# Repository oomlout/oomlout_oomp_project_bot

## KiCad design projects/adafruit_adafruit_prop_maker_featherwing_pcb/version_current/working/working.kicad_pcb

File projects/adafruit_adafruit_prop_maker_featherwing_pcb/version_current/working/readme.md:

# Adafruit-Prop-Maker-FeatherWing-PCB by adafruit  
This is a harvested standardized copy of a project from github.  
The original project can be found at:  
https://github.com/adafruit/Adafruit-Prop-Maker-FeatherWing-PCB  
Please consult that link for additional, details, files, and license information.  
Note: It was auto harvested and if the original repo had more than one board file or anything out of the ordinary the files here are likely not representative.

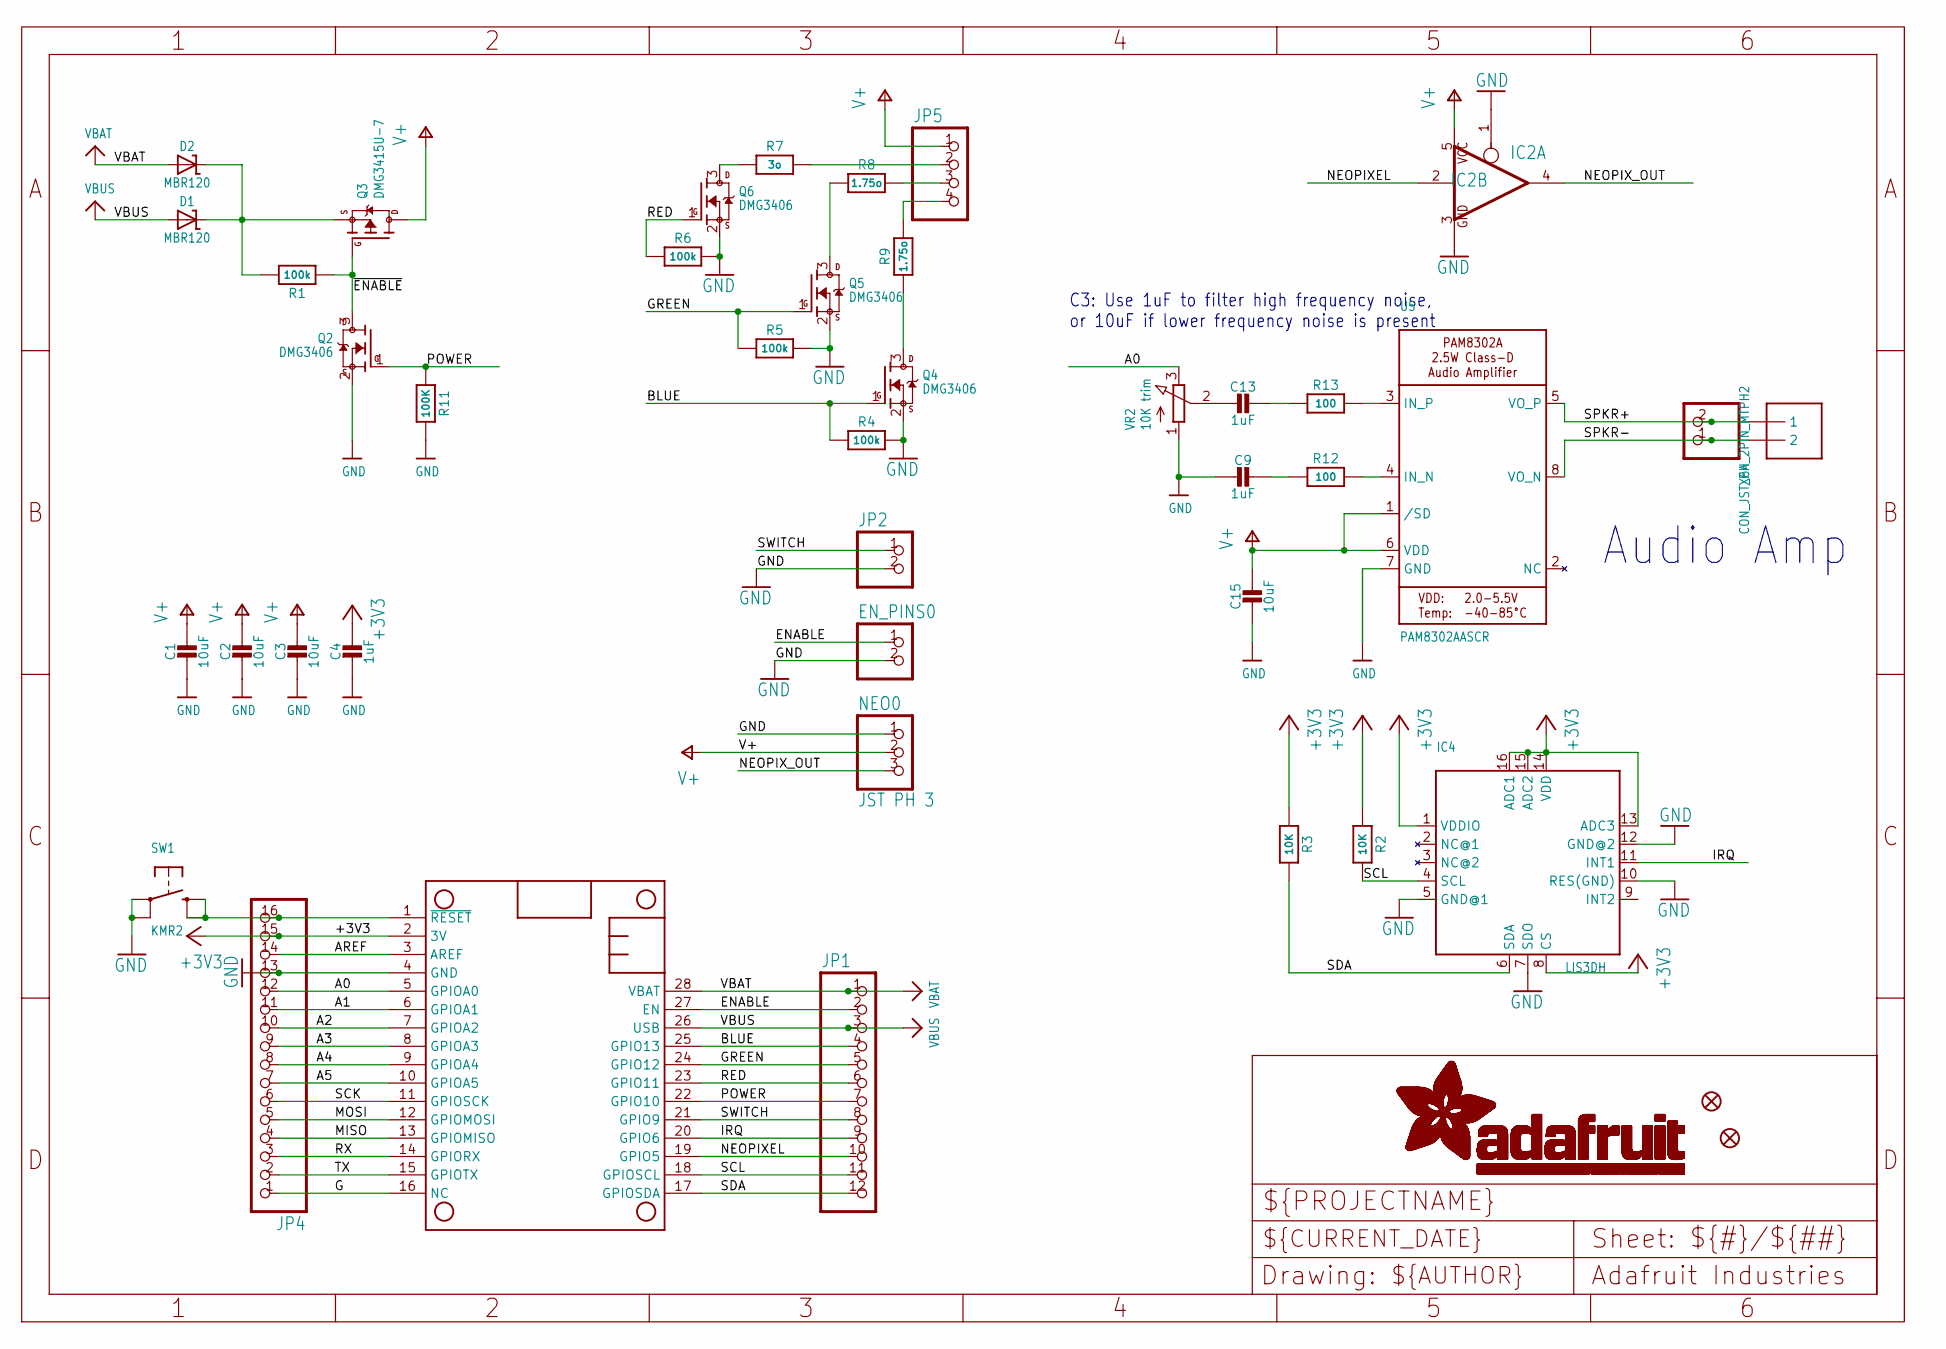
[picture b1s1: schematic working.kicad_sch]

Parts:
C1, C2, C3, C15: 10uF; 0805-NO
C4, C9, C13: 1uF; 0603-NO
D1, D2: MBR120; SOD-123
EN_PINS0: HEADER-1X2ROUND; 1X02_ROUND
FID1, FID3: FIDUCIAL_1MM
IC2: 741G125DBV; SOT23-5
IC4: LIS3DH; LGA16_3X3MM
JP1: HEADER-1X12; 1X12_ROUND
JP2: HEADER-1X2ROUND; 1X02_ROUND
JP4: HEADER-1X16ROUND; 1X16_ROUND
JP5: HEADER-1X4ROUND; 1X04_ROUND
MS1: FEATHERWING
NEO0: JST PH 3; JSTPH3
Q2, Q4, Q5, Q6: DMG3406; SOT23-WIDE
Q3: DMG3415U-7; SOT23-WIDE
R1, R4, R5, R6: 100k; 0603-NO
R2, R3: 10K; 0603-NO
R7: 3o; _1206
R8, R9: 1.75o; _1206
R11: 100K; 0603-NO
R12, R13: 100; 0603-NO
SW1: KMR2; BTN_KMR2_4.6X2.8
U5: PAM8302AASCR; MSOP8_0.65MM
U$1: CON_MOLEX_2P; 53398-0271
VR2: 10K trim; TRIMPOT_BOURNS_3303W
X6: CON_JST_PH_2PIN_MTPH2; JSTPH2

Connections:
+3V3: C4.1, IC4.1 (VDDIO), IC4.8 (CS), IC4.13 (ADC3), IC4.14 (VDD), IC4.15 (ADC2), IC4.16 (ADC1), JP4.15, MS1.2 (3V), R2.1, R3.1
A0: JP4.12, MS1.5 (GPIOA0), VR2.3 (E)
A1: JP4.11, MS1.6 (GPIOA1)
A2: JP4.10, MS1.7 (GPIOA2)
A3: JP4.9, MS1.8 (GPIOA3)
A4: JP4.8, MS1.9 (GPIOA4)
A5: JP4.7, MS1.10 (GPIOA5)
AREF: JP4.14, MS1.3 (AREF)
BLUE: JP1.4, MS1.25 (GPIO13), Q4.1 (G), R4.1
ENABLE: EN_PINS0.1, JP1.2, MS1.27 (EN)
G: JP4.1, MS1.16 (NC)
GND: C1.2, C2.2, C3.2, C4.2, C9.2, C15.2, EN_PINS0.2, IC2.1 (OE), IC2.3 (GND), IC4.5 (GND@1), IC4.7 (SDO), IC4.10 (RES(GND)), IC4.12 (GND@2), JP2.2, JP4.13, MS1.4 (GND), NEO0.1, Q2.2 (S), Q4.2 (S), Q5.2 (S), Q6.2 (S), R4.2, R5.2, R6.2, R11.2, SW1.A, SW1.A' (P1), U5.7 (GND), VR2.1 (A)
GREEN: JP1.5, MS1.24 (GPIO12), Q5.1 (G), R5.1
IRQ: IC4.11 (INT1), JP1.9, MS1.20 (GPIO6)
MISO: JP4.4, MS1.13 (GPIOMISO)
MOSI: JP4.5, MS1.12 (GPIOMOSI)
unnamed: Q6.3 (D), R7.1
unnamed: JP5.3, R8.2
unnamed: JP5.4, R9.2
unnamed: Q4.3 (D), R9.1
unnamed: Q5.3 (D), R8.1
unnamed: JP5.2, R7.2
unnamed: R12.2, U5.4 (IN_N)
unnamed: R13.2, U5.3 (IN_P)
unnamed: C9.1, R12.1
unnamed: C13.1, R13.1
unnamed: C13.2, VR2.2 (S)
unnamed: D1.C, D2.C, Q3.2 (S), R1.2
NEOPIXEL: IC2.2 (I), JP1.10, MS1.19 (GPIO5)
NEOPIX_OUT: IC2.4 (O), NEO0.3
POWER: JP1.7, MS1.22 (GPIO10), Q2.1 (G), R11.1
RED: JP1.6, MS1.23 (GPIO11), Q6.1 (G), R6.1
RESET: JP4.16, MS1.1 (~RESET), SW1.B (S), SW1.B' (S1)
RX: JP4.3, MS1.14 (GPIORX)
SCK: JP4.6, MS1.11 (GPIOSCK)
SCL: IC4.4 (SCL), JP1.11, MS1.18 (GPIOSCL), R2.2
SDA: IC4.6 (SDA), JP1.12, MS1.17 (GPIOSDA), R3.2
SPKR+: U5.5 (VO_P), U$1.1, X6.2
SPKR-: U5.8 (VO_N), U$1.2, X6.1
SWITCH: JP1.8, JP2.1, MS1.21 (GPIO9)
TX: JP4.2, MS1.15 (GPIOTX)
V+: C1.1, C2.1, C3.1, C15.1, IC2.5 (VCC), JP5.1, NEO0.2, Q3.3 (D), U5.1 (/SD), U5.6 (VDD)
VBAT: D2.A, JP1.1, MS1.28 (VBAT)
VBUS: D1.A, JP1.3, MS1.26 (USB)
~ENABLE: Q2.3 (D), Q3.1 (G), R1.1

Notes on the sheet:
Audio Amp
C3: Use 1uF to filter high frequency noise, or 10uF if lower frequency noise is present

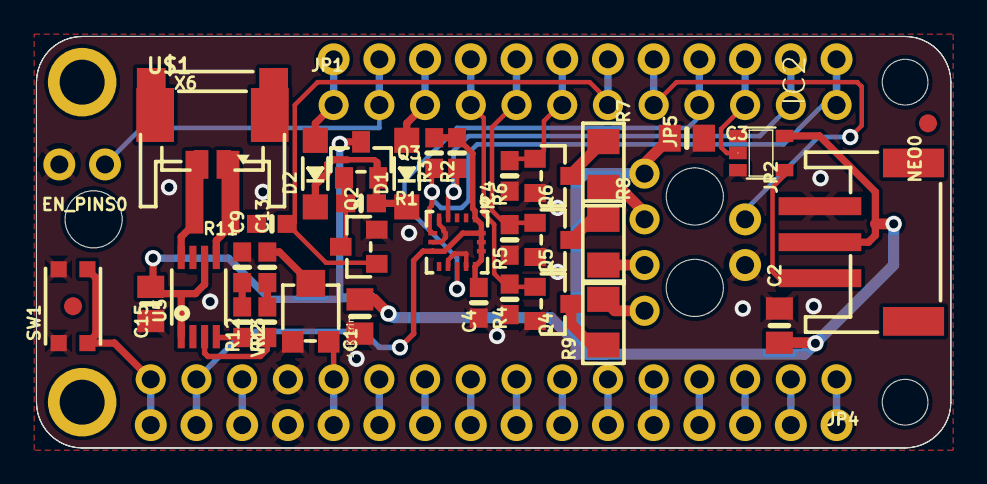
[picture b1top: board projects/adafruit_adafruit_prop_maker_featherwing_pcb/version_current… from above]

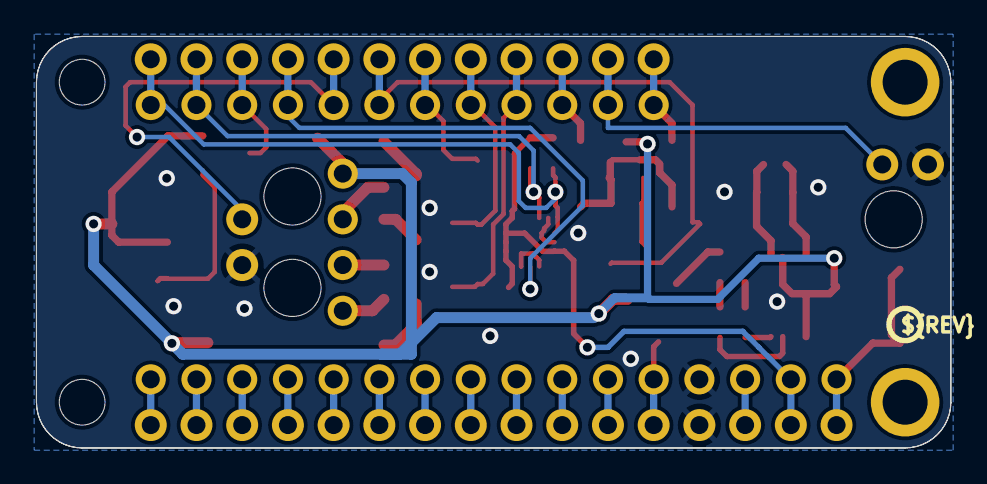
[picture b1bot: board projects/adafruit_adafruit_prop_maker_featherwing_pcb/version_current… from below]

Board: 2 copper layers, 50.8 x 22.9 mm, 48 parts (2 on the bottom side), 45 nets.

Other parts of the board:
@HOLE0, @HOLE1, @HOLE2: (no value)
U$6: PROPMAKER_BOT
U$14: PROPMAKER_TOP
U$15: PCBFEAT-REV-040

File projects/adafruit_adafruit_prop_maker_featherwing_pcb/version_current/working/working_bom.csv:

Row,Description,Part,References,Value,Footprint,Quantity Per PCB,Status,Datasheet
1,,CAP_CERAMIC0603_NO,C4 C9 C13,1uF,0603-NO,3, ,
2,,CAP_CERAMIC0805-NOOUTLINE,C1 C2 C3 C15,10uF,0805-NO,4, ,
3,,DIODE-SCHOTTKYSOD-123,D1 D2,MBR120,SOD-123,2, ,
4,,HEADER-1X2ROUND,EN_PINS0 JP2,HEADER-1X2ROUND,1X02_ROUND,2, ,
5,,741G125DBV,IC2,741G125DBV,SOT23-5,1, ,
6,,ACCEL_LIS3DHTR,IC4,LIS3DH,LGA16_3X3MM,1, ,
7,,HEADER-1X12,JP1,HEADER-1X12,1X12_ROUND,1, ,
8,,HEADER-1X16ROUND,JP4,HEADER-1X16ROUND,1X16_ROUND,1, ,
9,,HEADER-1X4ROUND,JP5,HEADER-1X4ROUND,1X04_ROUND,1, ,
10,,FEATHERWING,MS1,FEATHERWING,FEATHERWING,1, ,
11,,CON_JST_PH_3PIN,NEO0,JST PH 3,JSTPH3,1, ,
12,,MOSFET-NWIDE,Q2 Q4 Q5 Q6,DMG3406,SOT23-WIDE,4, ,
13,,MOSFET-PWIDE,Q3,DMG3415U-7,SOT23-WIDE,1, ,
14,,RESISTOR_1206,R8 R9,1.75o,_1206,2, ,
15,,RESISTOR_1206,R7,3o,_1206,1, ,
16,,RESISTOR_0603_NOOUT,R12 R13,100,0603-NO,2, ,
17,,RESISTOR_0603_NOOUT,R2 R3,10K,0603-NO,2, ,
18,,RESISTOR_0603_NOOUT,R1 R4 R5 R6 R11,100k,0603-NO,5, ,
19,,SWITCH_TACT_SMT4.6X2.8,SW1,KMR2,BTN_KMR2_4.6X2.8,1, ,
20,,AUDIOAMP_PAM8302A,U5,PAM8302AASCR,MSOP8_0.65MM,1, ,
21,,CON_MOLEX_2P,U$1,CON_MOLEX_2P,53398-0271,1, ,
22,,TRIMPOT3303W/X,VR2,10K trim,TRIMPOT_BOURNS_3303W,1, ,
23,,CON_JST_PH_2PIN_MTPH2,X6,CON_JST_PH_2PIN_MTPH2,JSTPH2,1, ,





Project info:
Schematic:,working
Variant:,default
Revision:,
Date:,2023-08-03_17-21-23
KiCad Version:,7.0.6-7.0.6~ubuntu22.04.1
Statistics:
Component Groups:,23
Component Count:,40 (0 SMD/ 0 THT)
Fitted Components:,40 (0 SMD/ 0 THT)
Number of PCBs:,1
Total Components:,40

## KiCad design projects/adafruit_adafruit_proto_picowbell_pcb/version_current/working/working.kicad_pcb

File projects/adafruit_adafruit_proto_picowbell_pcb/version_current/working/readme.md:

# Adafruit-Proto-PiCowbell-PCB by adafruit  
This is a harvested standardized copy of a project from github.  
The original project can be found at:  
https://github.com/adafruit/Adafruit-Proto-PiCowbell-PCB  
Please consult that link for additional, details, files, and license information.  
Note: It was auto harvested and if the original repo had more than one board file or anything out of the ordinary the files here are likely not representative.

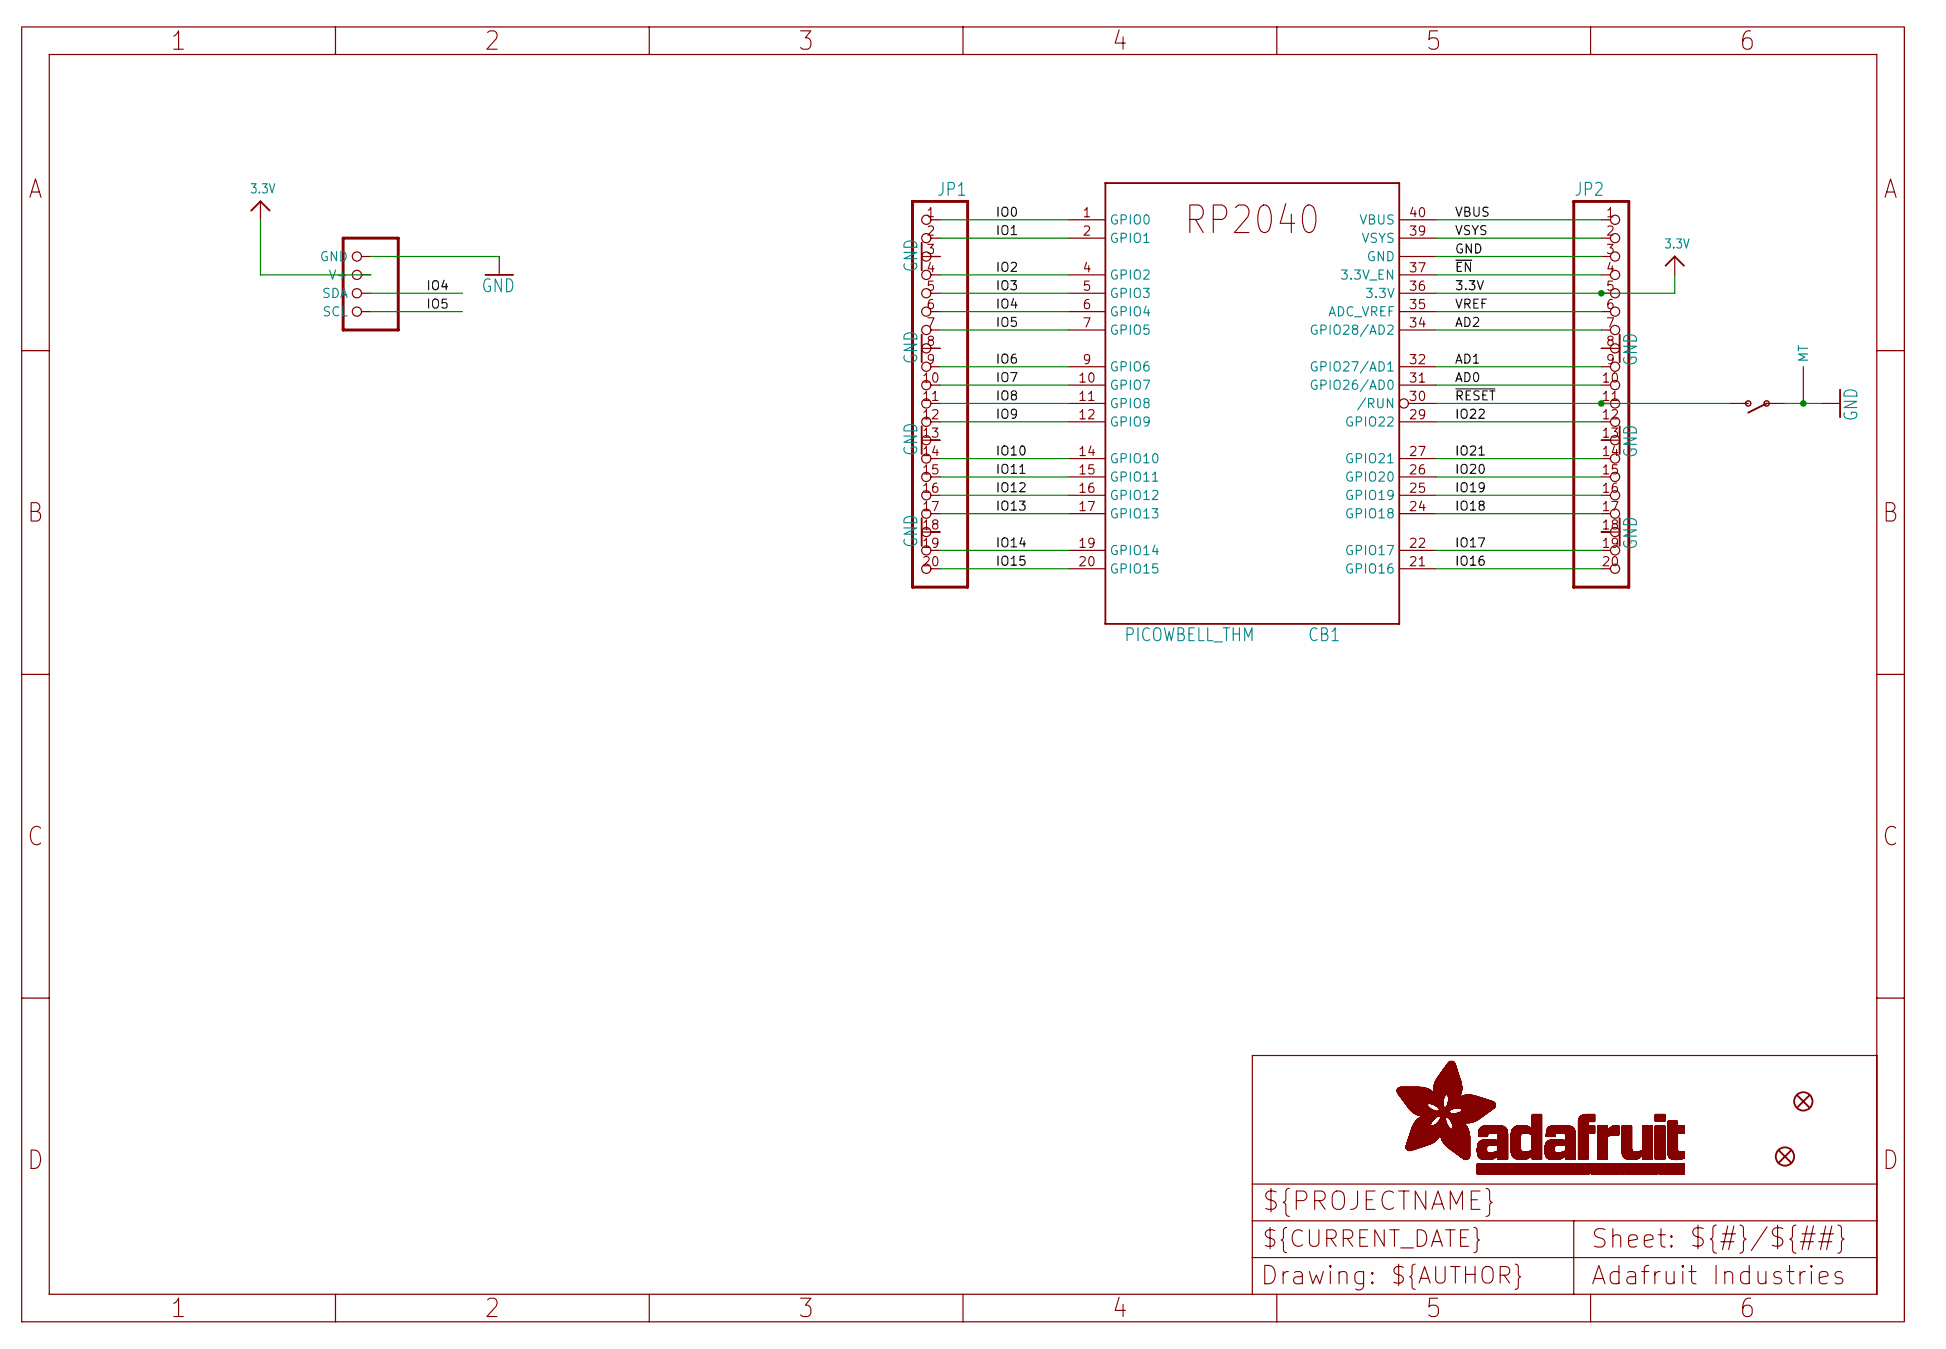
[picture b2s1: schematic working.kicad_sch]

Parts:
CB1: PICOWBELL_THM; PICOWBELL
CONN1: STEMMA_I2C_QT; JST_SH4
FID1, FID2: FIDUCIAL_1MM
JP1, JP2: HEADER-1X20_70MIL; 1X20_ROUND_70MIL
SW1: RA Tact; SPST_TACTILE_RA

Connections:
3.3V: CB1.36 (3.3V), CONN1.2 (V+), JP2.5
AD0: CB1.31 (GPIO26/AD0), JP2.10
AD1: CB1.32 (GPIO27/AD1), JP2.9
AD2: CB1.34 (GPIO28/AD2), JP2.7
GND: CB1.3 (GND), CB1.8 (GND), CB1.13 (GND), CB1.18 (GND), CB1.23 (GND), CB1.28 (GND), CB1.33 (GND), CB1.38 (GND), CONN1.1 (GND), JP1.3, JP1.8, JP1.13, JP1.18, JP2.3, JP2.8, JP2.13, JP2.18, SW1.1, SW1.MT1 (MT), SW1.MT2 (MT)
IO0: CB1.1 (GPIO0), JP1.1
IO1: CB1.2 (GPIO1), JP1.2
IO2: CB1.4 (GPIO2), JP1.4
IO3: CB1.5 (GPIO3), JP1.5
IO4: CB1.6 (GPIO4), CONN1.3 (SDA), JP1.6
IO5: CB1.7 (GPIO5), CONN1.4 (SCL), JP1.7
IO6: CB1.9 (GPIO6), JP1.9
IO7: CB1.10 (GPIO7), JP1.10
IO8: CB1.11 (GPIO8), JP1.11
IO9: CB1.12 (GPIO9), JP1.12
IO10: CB1.14 (GPIO10), JP1.14
IO11: CB1.15 (GPIO11), JP1.15
IO12: CB1.16 (GPIO12), JP1.16
IO13: CB1.17 (GPIO13), JP1.17
IO14: CB1.19 (GPIO14), JP1.19
IO15: CB1.20 (GPIO15), JP1.20
IO16: CB1.21 (GPIO16), JP2.20
IO17: CB1.22 (GPIO17), JP2.19
IO18: CB1.24 (GPIO18), JP2.17
IO19: CB1.25 (GPIO19), JP2.16
IO20: CB1.26 (GPIO20), JP2.15
IO21: CB1.27 (GPIO21), JP2.14
IO22: CB1.29 (GPIO22), JP2.12
VBUS: CB1.40 (VBUS), JP2.1
VREF: CB1.35 (ADC_VREF), JP2.6
VSYS: CB1.39 (VSYS), JP2.2
~EN: CB1.37 (3.3V_EN), JP2.4
~RESET: CB1.30 (/RUN), JP2.11, SW1.2 (S)

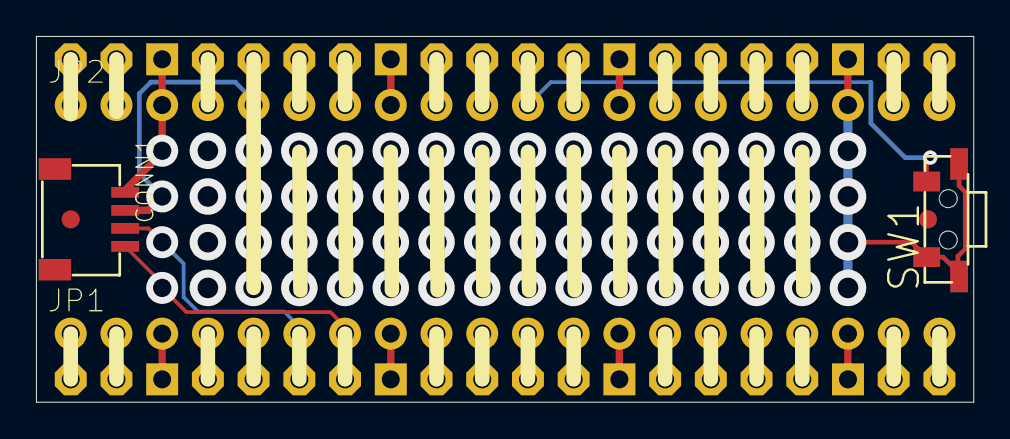
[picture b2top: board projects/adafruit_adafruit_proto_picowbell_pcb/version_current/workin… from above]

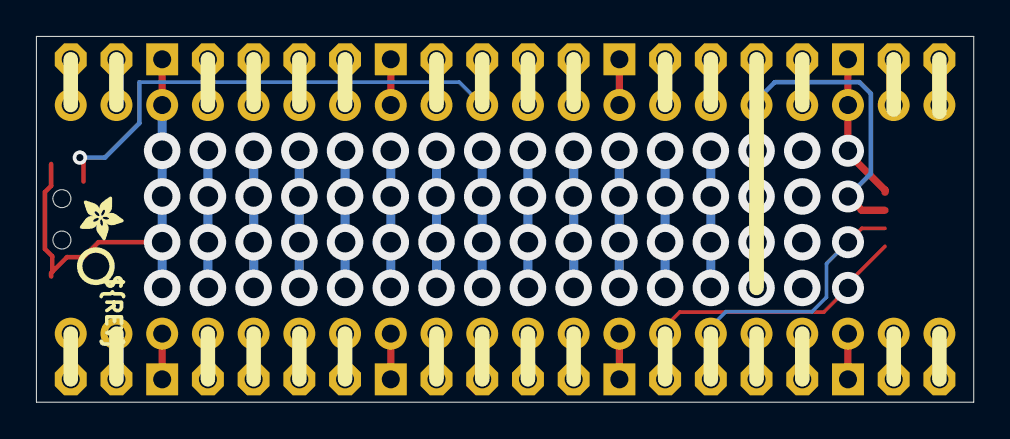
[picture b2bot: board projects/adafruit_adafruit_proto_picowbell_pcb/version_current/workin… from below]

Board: 2 copper layers, 52.1 x 20.3 mm, 77 parts (35 on the bottom side), 33 nets.

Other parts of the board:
PLABEL0: PLABEL0
PLABEL1: PLABEL1
PLABEL2: PLABEL2
PLABEL3: PLABEL3
PLABEL4: PLABEL4
PLABEL5: PLABEL5
PLABEL6: PLABEL6
PLABEL7: PLABEL7
PLABEL8: PLABEL8
PLABEL9: PLABEL9
PLABEL10: PLABEL10
PLABEL11: PLABEL11
PLABEL12: PLABEL12
PLABEL13: PLABEL13
PLABEL14: PLABEL14
PLABEL15: PLABEL15
PLABEL16: PLABEL16
PLABEL17: PLABEL17
PLABEL18: PLABEL18
PLABEL19: PLABEL19
PLABEL20: PLABEL20
PLABEL21: PLABEL21
PLABEL22: PLABEL22
PLABEL23: PLABEL23
PLABEL24: PLABEL24
PLABEL25: PLABEL25
PLABEL26: PLABEL26
PLABEL27: PLABEL27
PLABEL28: PLABEL28
PLABEL29: PLABEL29
PLABEL30: PLABEL30
PLABEL31: PLABEL31
PLABEL32: PLABEL32
PLABEL33: PLABEL33
PLABEL34: PLABEL34
PLABEL35: PLABEL35
PLABEL36: PLABEL36
PLABEL37: PLABEL37
PLABEL38: PLABEL38
PLABEL39: PLABEL39
PLABEL40: PLABEL40
PLABEL41: PLABEL41
PLABEL42: PLABEL42
PLABEL43: PLABEL43
PLABEL44: PLABEL44
PLABEL45: PLABEL45
PLABEL46: PLABEL46
PLABEL47: PLABEL47
PLABEL48: PLABEL48
PLABEL49: PLABEL49
PLABEL50: PLABEL50
PLABEL51: PLABEL51
PLABEL52: PLABEL52
PLABEL53: PLABEL53
PLABEL54: PLABEL54
PLABEL55: PLABEL55
PLABEL56: PLABEL56
PLABEL57: PLABEL57
PLABEL58: PLABEL58
PLABEL59: PLABEL59
PLABEL60: PLABEL60
PLABEL61: PLABEL61
PLABEL62: PLABEL62
PLABEL63: PLABEL63
PLABEL64: PLABEL64
PLABEL65: PLABEL65
PLABEL66: PLABEL66
PLABEL67: PLABEL67
U$2: ADAFRUIT_2.5MM
U$6: PCBFEAT-REV-040

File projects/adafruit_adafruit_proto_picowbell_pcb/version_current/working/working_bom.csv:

Row,Description,Part,References,Value,Footprint,Quantity Per PCB,Status,Datasheet
1,,PICOWBELL_THM,CB1,PICOWBELL_THM,PICOWBELL,1, ,
2,,STEMMA_I2C_QT,CONN1,STEMMA_I2C_QT,JST_SH4,1, ,
3,,HEADER-1X20_70MIL,JP1 JP2,HEADER-1X20_70MIL,1X20_ROUND_70MIL,2, ,
4,,SWITCH_SPST_MNT_TACT_RA,SW1,RA Tact,SPST_TACTILE_RA,1, ,





Project info:
Schematic:,working
Variant:,default
Revision:,
Date:,2023-08-03_17-21-23
KiCad Version:,7.0.6-7.0.6~ubuntu22.04.1
Statistics:
Component Groups:,4
Component Count:,5 (0 SMD/ 0 THT)
Fitted Components:,5 (0 SMD/ 0 THT)
Number of PCBs:,1
Total Components:,5

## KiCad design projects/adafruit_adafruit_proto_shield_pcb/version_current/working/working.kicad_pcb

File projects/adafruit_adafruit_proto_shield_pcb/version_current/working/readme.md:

# OOMP Project  
## Adafruit-Proto-Shield-PCB  by adafruit  
  
oomp key: oomp_projects_flat_adafruit_adafruit_proto_shield_pcb  
(snippet of original readme)  
  
-- Adafruit Proto Shield for Arduino Unassembled Kit - Stackable - Version R3 PCB  
  
<a href="http://www.adafruit.com/products/2077"><br/>  
Click here to purchase one from the Adafruit shop</a>  
  
PCB files for the Adafruit Proto Shield for Arduino Unassembled Kit - Stackable - Version R3. Format is EagleCAD schematic and board layout  
* https://www.adafruit.com/product/2077  
  
--- Description  
  
This prototyping shield is the best out there (well, we think so, at least), and now is even better with **Version R3** - updated for the most compatibility with just about all the Arduinos! It works with UNO, Mega, Leonardo, NG, Diecimila, Duemilanove, and compatible Arduinos. Yun's and Arduino Ethernets have a chunky Ethernet jack that gets in the way of stacking, you can use the stacking headers included and it will work, just doesn't sit nice and flat.  
  
Check out these awesome specifications:  
  
 * It has a nice standard 0.1"x0.1" prototying grid with big pads  
 * Comes with Stacking headers and plain header, choose whichever you want when soldering together  
 * A IC pattern for adding DIP ICs up to 20 pins  
 * Power rails down the middle and sides  
 * A reset button and an extra general use button  
 * 2 3mm general use LEDs, red and green, as well as 2 matching resistors  
 * A pass-thru ICSP stacking header so you can stack any kind of shield on top, and/or use an AVR programmer  
 * A surface-mount chip area for up to 14 SOIC size parts  
 * Compatib  
  full source readme at [readme_src.md](readme_src.md)  
  
source repo at: [https://github.com/adafruit/Adafruit-Proto-Shield-PCB](https://github.com/adafruit/Adafruit-Proto-Shield-PCB)  
## Board  

## Schematic  

[schematic pdf](working_schematic.pdf)  
## Images

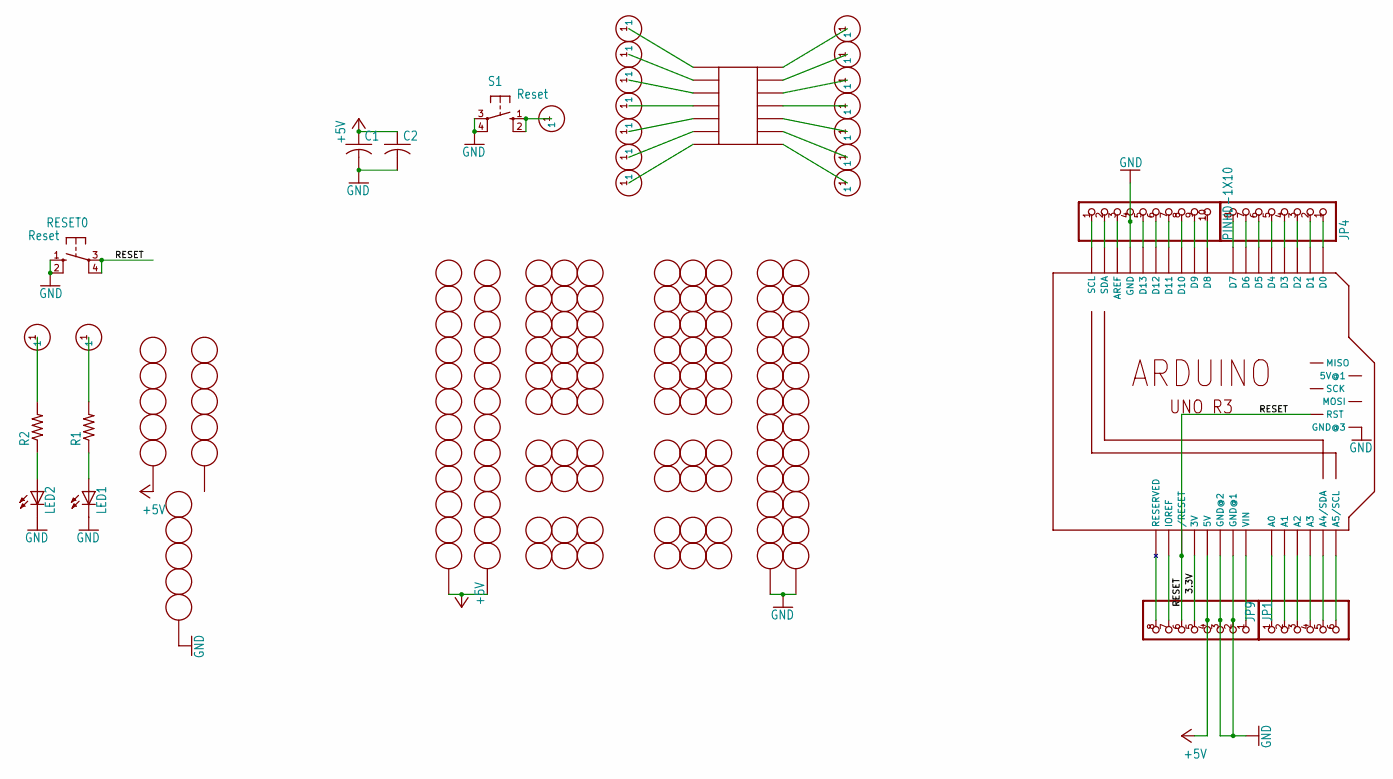
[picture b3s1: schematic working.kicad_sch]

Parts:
C1, C2: C-US025-025X050; C025-025X050
GNDSTRIP1, GNDSTRIP2: 12-STRIP
IC1: SMD-14; SO-14NMW
JP1, JP4: PINHD-1X8BIG; 1X08-BIG
JP9: PINHD-1X6B; 1X06-BIG
LED1, LED2: LED3MM
M1: ARDUINO_R3_ICSP; ARDUINOR3_ICSP
R1, R2: R-US_0207/5V; 0207_5V
RESET0: Reset; B3F-10XX
S1: Reset; B3F-10XX
U$1: PINHD-1X10; 1X10-BIG
U$2, U$4, U$6, U$7, U$8, U$9, U$16, U$19, U$25, U$27, U$34, U$35, U$37, U$38, U$39, U$40, U$41: PERFHOLE
U$3, U$24, U$43: 5-STRIP
U$5, U$10, U$11, U$12, U$13, U$14, U$15, U$17, U$18, U$20, U$21, U$22, U$23, U$26, U$28, U$29, U$30, U$31, U$32, U$33: 3-STRIP
VCCSTRIP1, VCCSTRIP2: 12-STRIP

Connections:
3.3V: JP1.5, M1.3V
+5V: C1.1, C2.1, JP1.4, M1.5V, U$24.P$3, VCCSTRIP1.P$1, VCCSTRIP2.P$1
GND: C1.2, C2.2, GNDSTRIP1.P$1, GNDSTRIP2.P$1, JP1.2, JP1.3, LED1.K (C), LED2.K (C), M1.GND, M1.GND@1 (GND@2), M1.GND@2 (GND@3), M1.GND@3 (GND@1), RESET0.1 (S), RESET0.2 (S1), S1.3, S1.4 (P1), U$1.4, U$43.P$3
unnamed: M1.AREF, U$1.3
unnamed: JP1.8, M1.RESERVED
unnamed: M1.D13, U$1.5
unnamed: LED1.A, R1.1
unnamed: JP1.7, M1.IOREF
unnamed: R1.2, U$7.1
unnamed: R2.2, U$4.1
unnamed: LED2.A, R2.1
unnamed: M1.D12, U$1.6
unnamed: M1.D11, U$1.7
unnamed: M1.D10, U$1.8
unnamed: M1.D9, U$1.9
unnamed: M1.D8, U$1.10
unnamed: JP9.1, M1.A0
unnamed: JP9.2, M1.A1
unnamed: JP9.3, M1.A2
unnamed: JP9.4, M1.A3
unnamed: JP9.5, M1.A4 (A4/SDA)
unnamed: JP9.6, M1.A5 (A5/SCL)
unnamed: JP4.1, M1.D0
unnamed: JP4.2, M1.D1
unnamed: JP4.3, M1.D2
unnamed: JP4.4, M1.D3
unnamed: JP4.5, M1.D4
unnamed: IC1.P$1, U$2.1
unnamed: IC1.P$2, U$6.1
unnamed: JP4.6, M1.D5
unnamed: JP4.7, M1.D6
unnamed: IC1.P$3, U$8.1
unnamed: IC1.P$4, U$9.1
unnamed: IC1.P$5, U$19.1
unnamed: JP4.8, M1.D7
unnamed: JP1.1, M1.VIN
unnamed: M1.SCL, U$1.1
unnamed: IC1.P$6, U$25.1
unnamed: IC1.P$7, U$27.1
unnamed: IC1.P$8, U$34.1
unnamed: IC1.P$9, U$35.1
unnamed: IC1.P$10, U$37.1
unnamed: M1.SDA, U$1.2
unnamed: IC1.P$11, U$38.1
unnamed: IC1.P$12, U$39.1
unnamed: IC1.P$13, U$40.1
unnamed: IC1.P$14, U$41.1
unnamed: S1.1 (S), S1.2 (S1), U$16.1
RESET: JP1.6, M1.RESET (/RESET), M1.RESET_ICSP (RST), RESET0.3, RESET0.4 (P1)

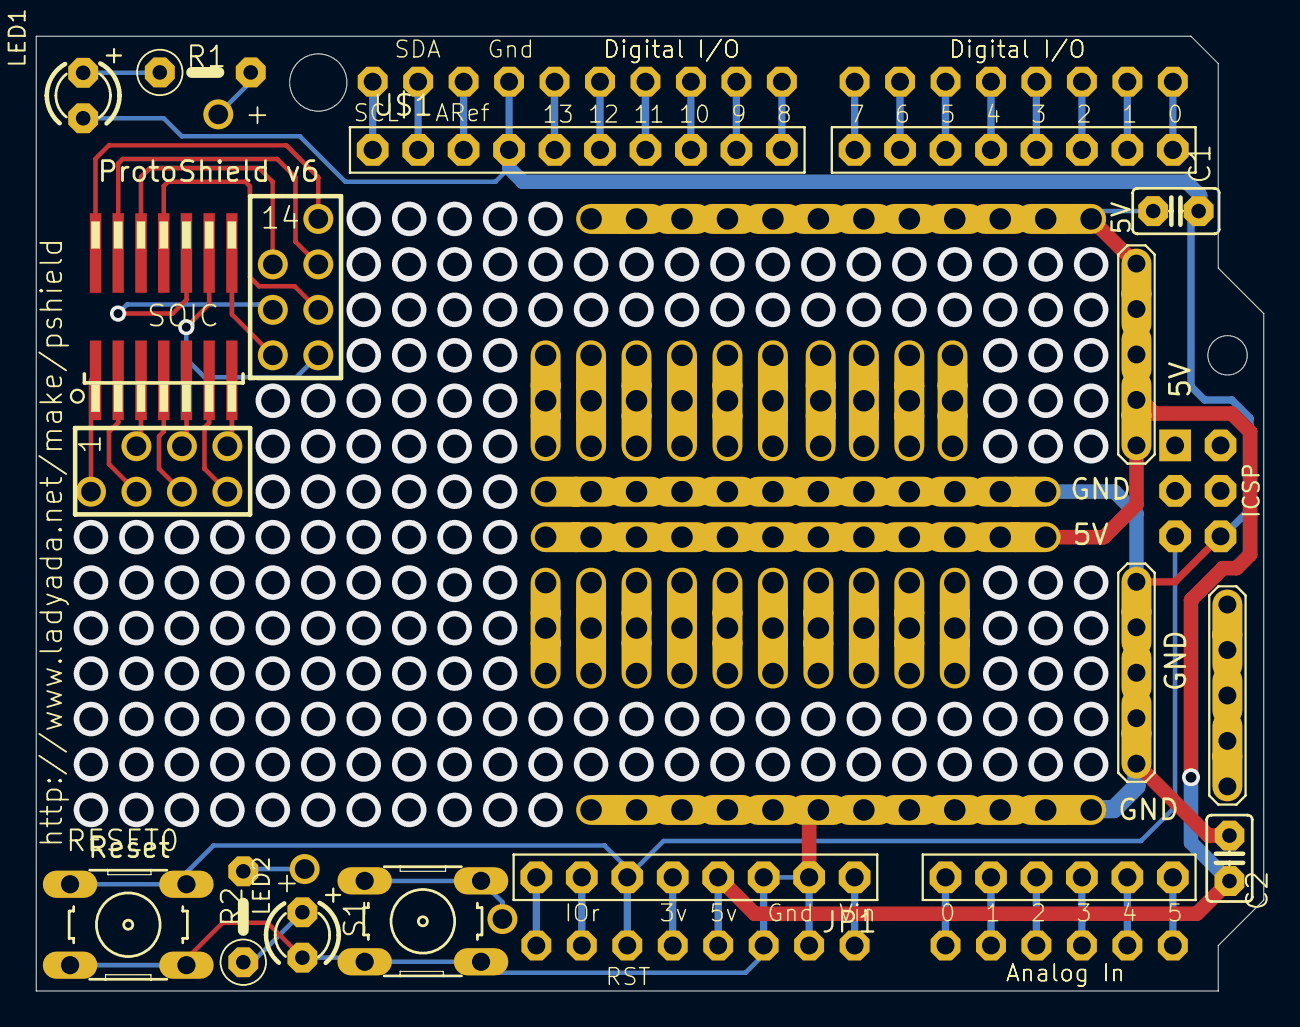
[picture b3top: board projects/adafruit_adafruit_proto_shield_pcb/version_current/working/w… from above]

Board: 2 copper layers, 68.6 x 53.3 mm, 61 parts (1 on the bottom side), 49 nets.

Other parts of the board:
@HOLE0, @HOLE1: (no value)
U$36: ADAFRUIT_9MM

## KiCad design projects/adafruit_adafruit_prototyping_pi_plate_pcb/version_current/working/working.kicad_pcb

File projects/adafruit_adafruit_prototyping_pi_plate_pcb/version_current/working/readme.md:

# Adafruit-Prototyping-Pi-Plate-PCB by adafruit  
This is a harvested standardized copy of a project from github.  
The original project can be found at:  
https://github.com/adafruit/Adafruit-Prototyping-Pi-Plate-PCB  
Please consult that link for additional, details, files, and license information.  
Note: It was auto harvested and if the original repo had more than one board file or anything out of the ordinary the files here are likely not representative.

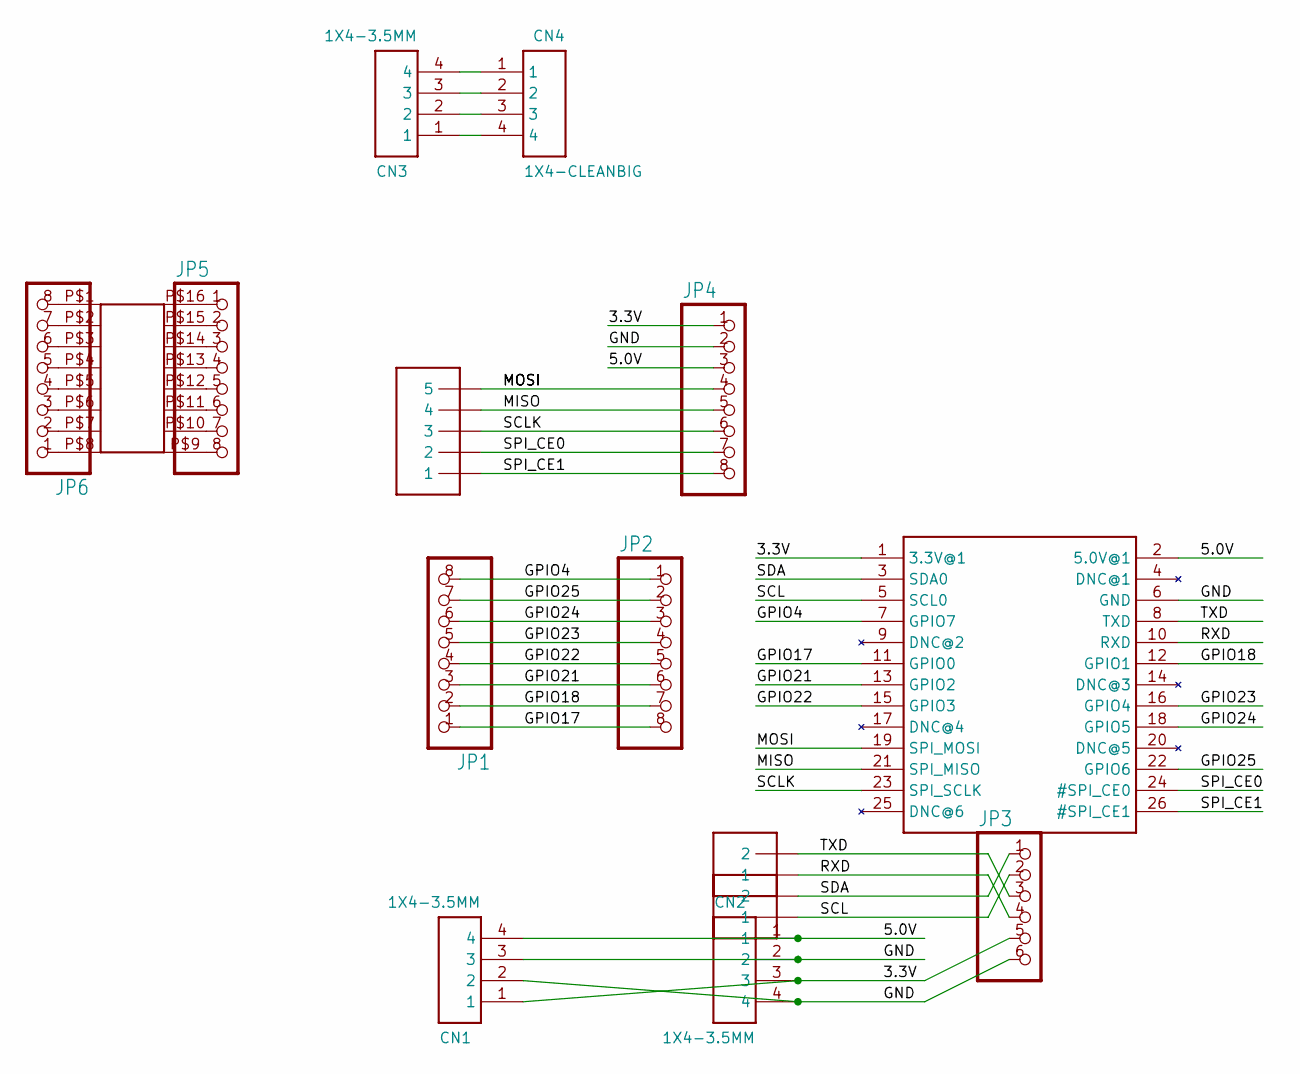
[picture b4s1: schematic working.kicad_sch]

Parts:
CN1, CN2, CN3: 1X4-3.5MM; 1X04-3.5MM
CN4: 1X4-CLEANBIG; 1X04-CLEANBIG
J1, J2: 1X2-3.5MM
J3: 1X5; 1X05-3.5MM
JP1: PINHD-1X8-3.5MM; 1X08-3.5MM
JP2, JP4, JP5, JP6: PINHD-1X8BIG; 1X08-BIG
JP3: PINHD-1X6B; 1X06-BIG
U$1: RASPBERRYPI_BB; RASBERRYPI_SHIELD
U$2: SMD-16SOIC; SO-16NMW

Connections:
3.3V: CN1.1, CN2.3, JP3.5, JP4.1, U$1.1 (3.3V@1)
5.0V: CN1.4, CN2.1, JP4.3, U$1.2 (5.0V@1)
GND: CN1.2, CN1.3, CN2.2, CN2.4, JP3.6, JP4.2, U$1.6 (GND)
GPIO4: JP1.8, JP2.1, U$1.7 (GPIO7)
GPIO17: JP1.1, JP2.8, U$1.11 (GPIO0)
GPIO18: JP1.2, JP2.7, U$1.12 (GPIO1)
GPIO21: JP1.3, JP2.6, U$1.13 (GPIO2)
GPIO22: JP1.4, JP2.5, U$1.15 (GPIO3)
GPIO23: JP1.5, JP2.4, U$1.16 (GPIO4)
GPIO24: JP1.6, JP2.3, U$1.18 (GPIO5)
GPIO25: JP1.7, JP2.2, U$1.22 (GPIO6)
MISO: J3.4, JP4.5, U$1.21 (SPI_MISO)
MOSI: J3.5, JP4.4, U$1.19 (SPI_MOSI)
unnamed: JP5.1, U$2.P$16
unnamed: JP5.2, U$2.P$15
unnamed: JP5.3, U$2.P$14
unnamed: JP5.4, U$2.P$13
unnamed: JP5.5, U$2.P$12
unnamed: JP5.6, U$2.P$11
unnamed: JP5.7, U$2.P$10
unnamed: JP5.8, U$2.P$9
unnamed: JP6.1, U$2.P$8
unnamed: JP6.2, U$2.P$7
unnamed: JP6.3, U$2.P$6
unnamed: JP6.4, U$2.P$5
unnamed: JP6.5, U$2.P$4
unnamed: JP6.6, U$2.P$3
unnamed: JP6.7, U$2.P$2
unnamed: JP6.8, U$2.P$1
unnamed: CN3.4, CN4.1
unnamed: CN3.3, CN4.2
unnamed: CN3.2, CN4.3
unnamed: CN3.1, CN4.4
RXD: J2.1, JP3.4, U$1.10 (RXD)
SCL: J1.1, JP3.2, U$1.5 (SCL0)
SCLK: J3.3, JP4.6, U$1.23 (SPI_SCLK)
SDA: J1.2, JP3.1, U$1.3 (SDA0)
SPI_CE0: J3.2, JP4.7, U$1.24 (#SPI_CE0)
SPI_CE1: J3.1, JP4.8, U$1.26 (#SPI_CE1)
TXD: J2.2, JP3.3, U$1.8 (TXD)

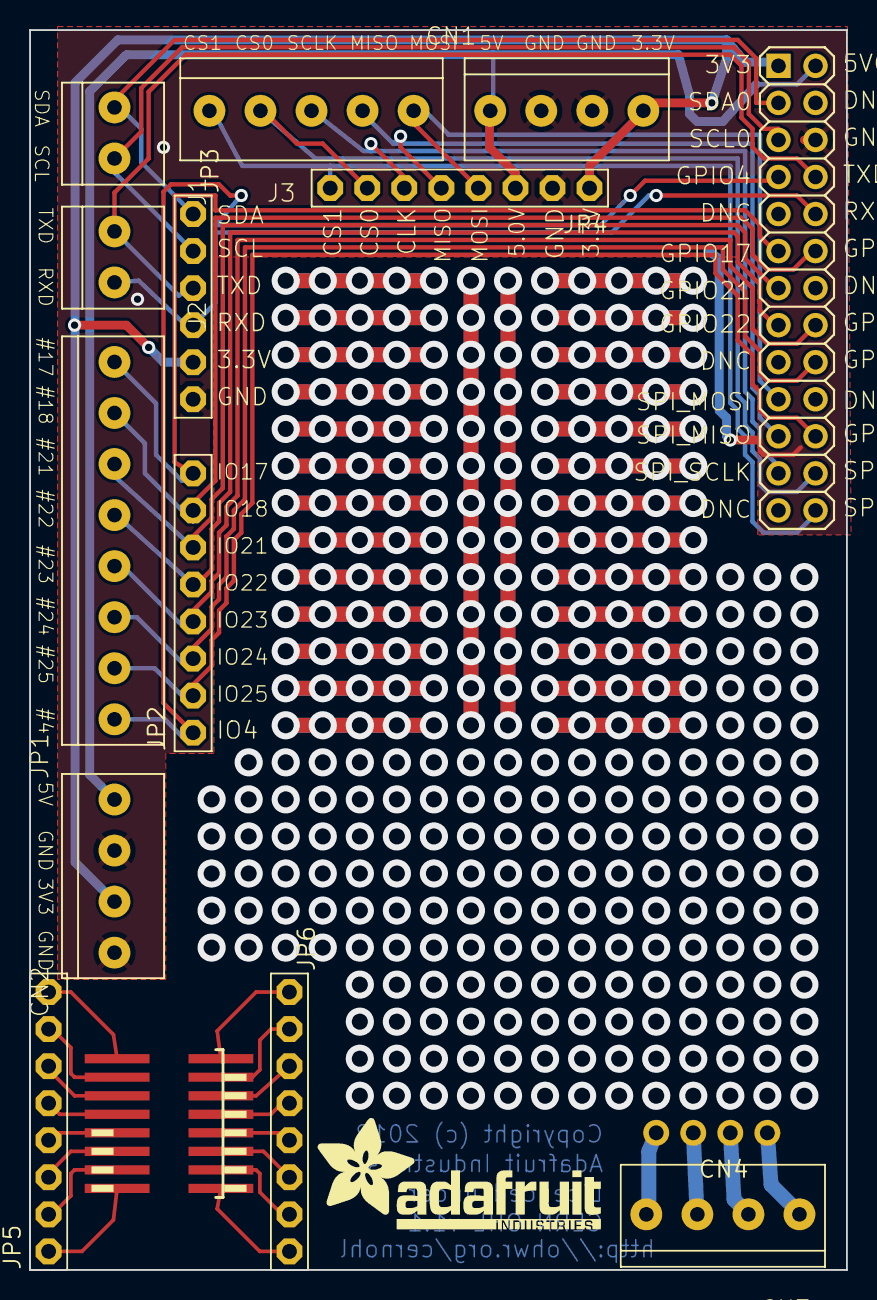
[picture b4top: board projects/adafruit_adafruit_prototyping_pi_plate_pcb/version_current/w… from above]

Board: 16 copper layers, 56.0 x 85.0 mm, 16 parts (0 on the bottom side), 40 nets.

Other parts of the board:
U$3: ADAFRUIT_TEXT_20MM

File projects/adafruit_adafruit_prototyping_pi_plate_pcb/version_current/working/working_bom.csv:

Row,Description,Part,References,Value,Footprint,Quantity Per PCB,Status,Datasheet
1,,1X4-3.5MM,CN1 CN2 CN3,1X4-3.5MM,1X04-3.5MM,3, ,
2,,1X4-CLEANBIG,CN4,1X4-CLEANBIG,1X04-CLEANBIG,1, ,
3,,1X2-3.5MM,J1 J2,1X2-3.5MM,1X2-3.5MM,2, ,
4,,1X5,J3,1X5,1X05-3.5MM,1, ,
5,,PINHD-1X6B,JP3,PINHD-1X6B,1X06-BIG,1, ,
6,,PINHD-1X8-3.5MM,JP1,PINHD-1X8-3.5MM,1X08-3.5MM,1, ,
7,,PINHD-1X8BIG,JP2 JP4 JP5 JP6,PINHD-1X8BIG,1X08-BIG,4, ,
8,,RASPBERRYPI_BB,U$1,RASPBERRYPI_BB,RASBERRYPI_SHIELD,1, ,
9,,SMD-16SOIC,U$2,SMD-16SOIC,SO-16NMW,1, ,





Project info:
Schematic:,working
Variant:,default
Revision:,
Date:,2023-08-03_17-21-23
KiCad Version:,7.0.6-7.0.6~ubuntu22.04.1
Statistics:
Component Groups:,9
Component Count:,15 (0 SMD/ 0 THT)
Fitted Components:,15 (0 SMD/ 0 THT)
Number of PCBs:,1
Total Components:,15

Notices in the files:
projects/adafruit_adafruit_prototyping_pi_plate_pcb/version_current/working/working.kicad_pcb:
Copyright (c) 2012
CERN OHL v1.1
Licenced under
B.Cu
